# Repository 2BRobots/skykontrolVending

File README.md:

# skykontrolVending
This repository contains all the hardware and software used by 2BRobots to create and support IoT vending machines.

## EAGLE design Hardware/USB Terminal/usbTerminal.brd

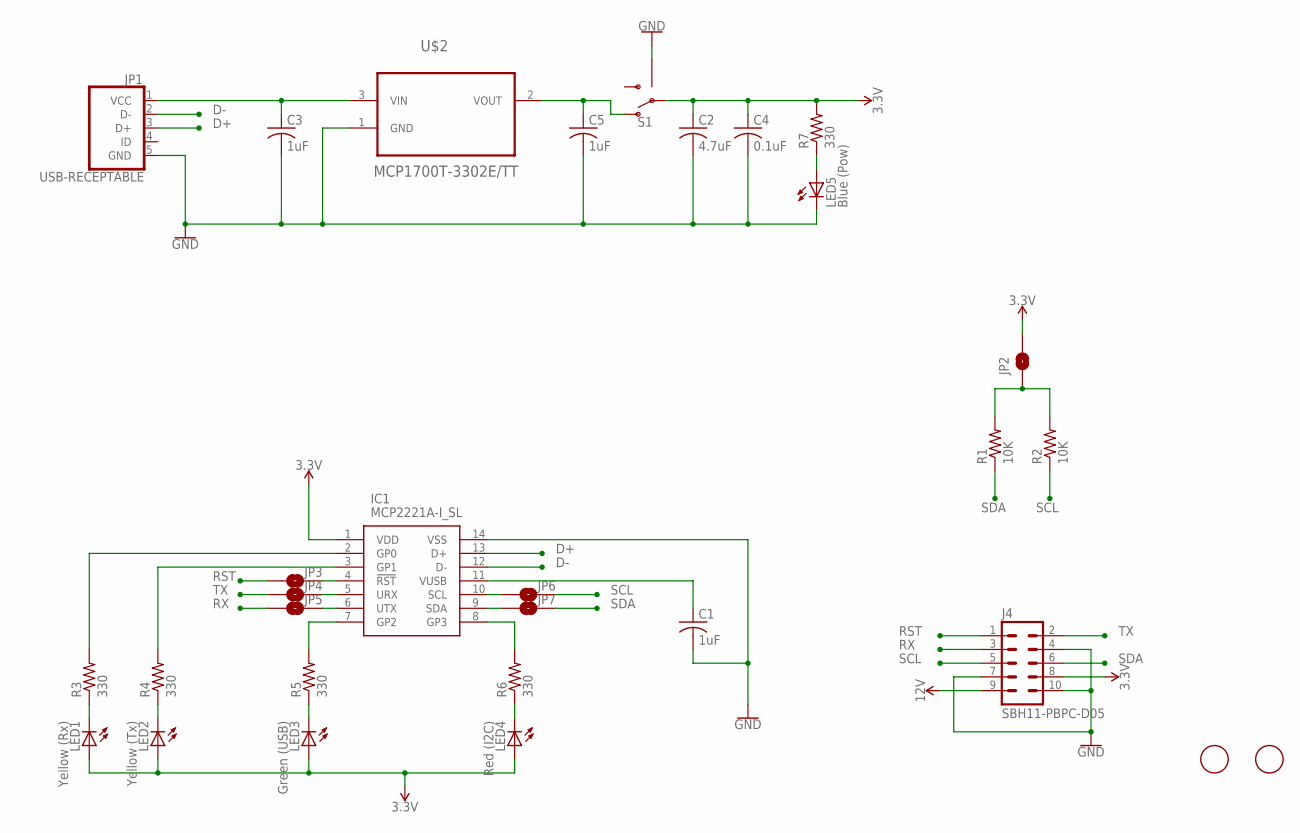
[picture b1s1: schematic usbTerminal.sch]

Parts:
C1, C3, C5: 1uF; C0603K
C2: 4.7uF; C0805K
C4: 0.1uF; C0603K
IC1: MCP2221A-I_SL; SOIC127P600X175-14N
J4: SBH11-PBPC-D05
JP1: USB-RECEPTABLE; FCI-10103594-0001LF
JP2, JP3, JP4, JP5, JP6, JP7: JUMPER-SMT_2_NO_SILK; SMT-JUMPER_2_NO_SILK
LED1: Yellow (Rx); CHIPLED_1206
LED2: Yellow (Tx); CHIPLED_1206
LED3: Green (USB); CHIPLED_1206
LED4: Red (I2C); CHIPLED_1206
LED5: Blue (Pow); CHIPLED_1206
R1, R2: 10K; R0805
R3, R4, R5, R6, R7: 330; R0805
S1: SWITCH-SPDT-SMD-RIGHT-ANGLE; SWITCH_SPST_SMD_A
U$1, U$3: FIDUCIAL; FIDUCIAL_1MM
U$2: MCP1700T-3302E/TT; SOT95P237X112-3N

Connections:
3.3V: C2.1, C4.1, IC1.1 (VDD), J4.8, JP2.2, LED1.A, LED2.A, LED3.A, LED4.A, R7.2, S1.2
12V: J4.9
D+: IC1.13 (D+), JP1.3 (D+)
D-: IC1.12 (D-), JP1.2 (D-)
GND: C1.2, C2.2, C3.2, C4.2, C5.2, IC1.14 (VSS), J4.4, J4.7, J4.10, JP1.5 (GND), LED5.C, S1.GND1 (GND), S1.GND2 (GND), S1.GND3 (GND), S1.GND4 (GND), U$2.1 (GND)
unnamed: IC1.4 (!RST), JP3.1
unnamed: C1.1, IC1.11 (VUSB)
unnamed: IC1.5 (URX), JP4.1
unnamed: JP2.1, R1.2, R2.2
unnamed: IC1.6 (UTX), JP5.1
unnamed: IC1.10 (SCL), JP6.2
unnamed: IC1.9 (SDA), JP7.2
unnamed: LED1.C, R3.1
unnamed: LED2.C, R4.1
unnamed: LED3.C, R5.1
unnamed: LED4.C, R6.1
unnamed: C3.1, JP1.1 (VCC), U$2.3 (VIN)
unnamed: LED5.A, R7.1
unnamed: IC1.7 (GP2), R5.2
unnamed: IC1.8 (GP3), R6.2
unnamed: IC1.3 (GP1), R4.2
unnamed: IC1.2 (GP0), R3.2
unnamed: C5.1, S1.1 (O), U$2.2 (VOUT)
RST: J4.1, JP3.2
RX: J4.3, JP5.2
SCL: J4.5, JP6.1, R2.1
SDA: J4.6, JP7.1, R1.1
TX: J4.2, JP4.2

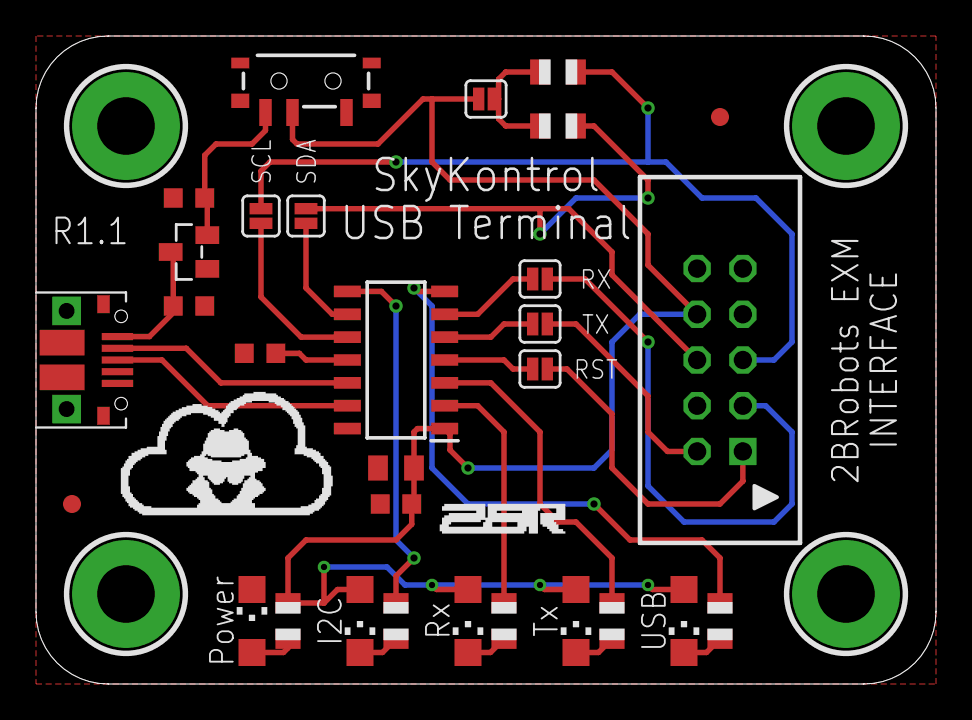
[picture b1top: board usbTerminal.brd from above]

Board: 2 copper layers, 50.0 x 36.0 mm, 30 parts (0 on the bottom side), 27 nets.

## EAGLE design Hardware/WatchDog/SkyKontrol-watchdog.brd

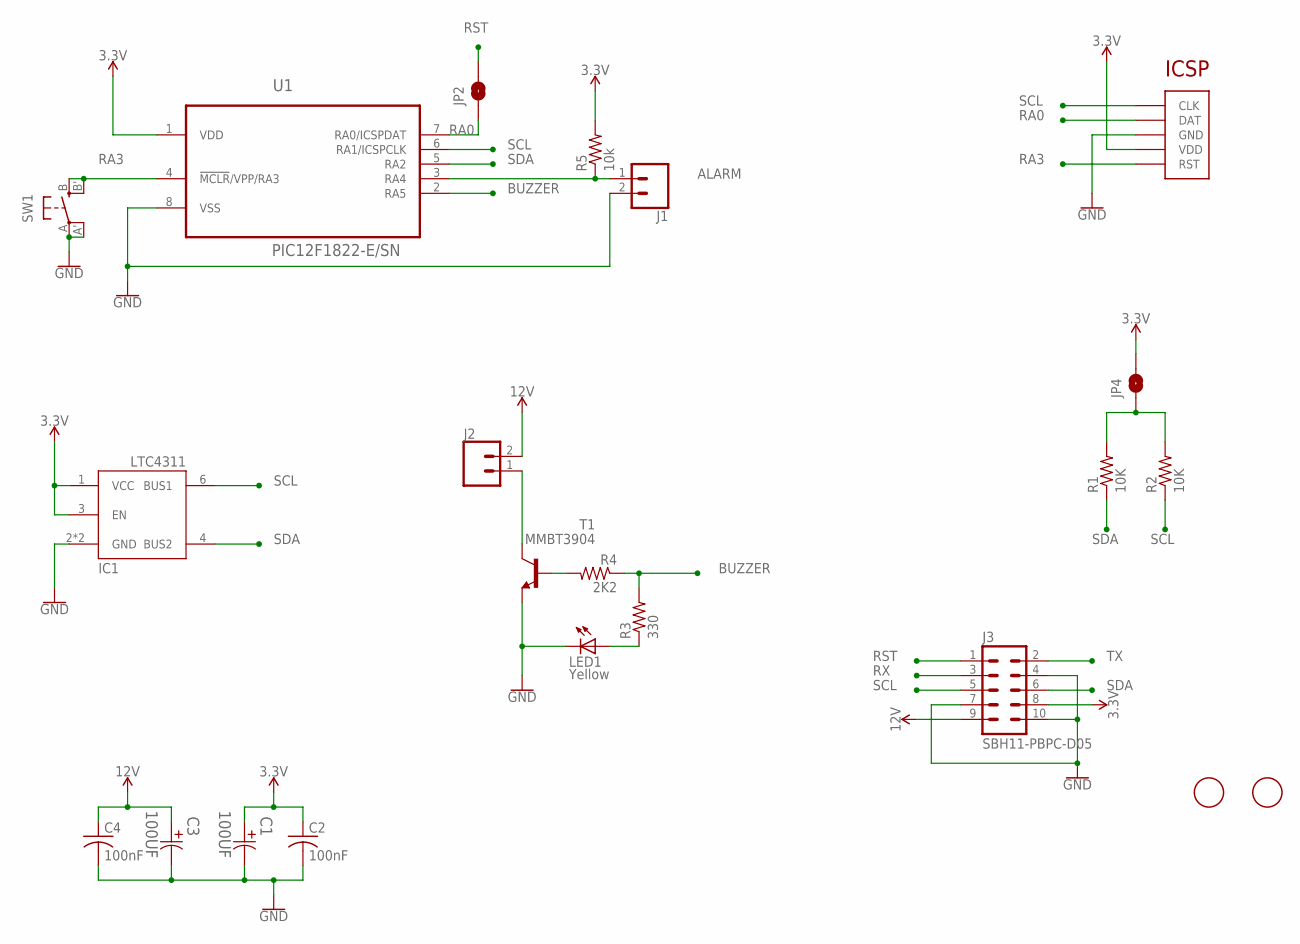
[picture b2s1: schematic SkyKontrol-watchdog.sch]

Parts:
C1, C3: 100UF; CAPAE660X800N
C2, C4: 100nF; C0603K
IC1: LTC4311_SC70; SC70-6L
J1, J2: CONN_025MM; SCREWTERMINAL-5MM-2
J3: SBH11-PBPC-D05
JP2, JP4: JUMPER-SMT_2_NO_SILK; SMT-JUMPER_2_NO_SILK
LED1: Yellow; CHIPLED_1206
R1, R2: 10K; R0805
R3: 330; R0805
R4: 2K2; R0805
R5: 10k; R0805
SW1: SPST_TACT-EVQQ2; EVQ-Q2
T1: MMBT3904; SOT23-BEC
U1: PIC12F1822-E/SN; SOIC127P600X175-8N
U$1, U$3: FIDUCIAL; FIDUCIAL_1MM
U$2: ICSP_POGO

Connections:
3.3V: C1.1, C2.1, IC1.1 (VCC), IC1.3 (EN), J3.8, JP4.2, R5.2, U1.1 (VDD), U$2.P$2 (VDD)
12V: C3.1, C4.1, J2.2, J3.9
ALARM: J1.1, R5.1, U1.3 (RA4)
BUZZER: R3.2, R4.1, U1.2 (RA5)
GND: C1.2, C2.2, C3.2, C4.2, IC1.2 (GND), IC1.5 (GND), J1.2, J3.4, J3.7, J3.10, LED1.C, SW1.A, SW1.A' (P1), T1.E, U1.8 (VSS), U$2.P$3 (GND)
unnamed: LED1.A, R3.1
unnamed: J2.1, T1.C
unnamed: JP4.1, R1.2, R2.2
unnamed: R4.2, T1.B
RA0: JP2.1, U1.7 (RA0/ICSPDAT), U$2.P$4 (DAT)
RA3: SW1.B (S), SW1.B' (S1), U1.4 (!MCLR!/VPP/RA3), U$2.P$1 (RST)
RST: J3.1, JP2.2
RX: J3.3
SCL: IC1.6 (BUS1), J3.5, R2.1, U1.6 (RA1/ICSPCLK), U$2.P$5 (CLK)
SDA: IC1.4 (BUS2), J3.6, R1.1, U1.5 (RA2)
TX: J3.2

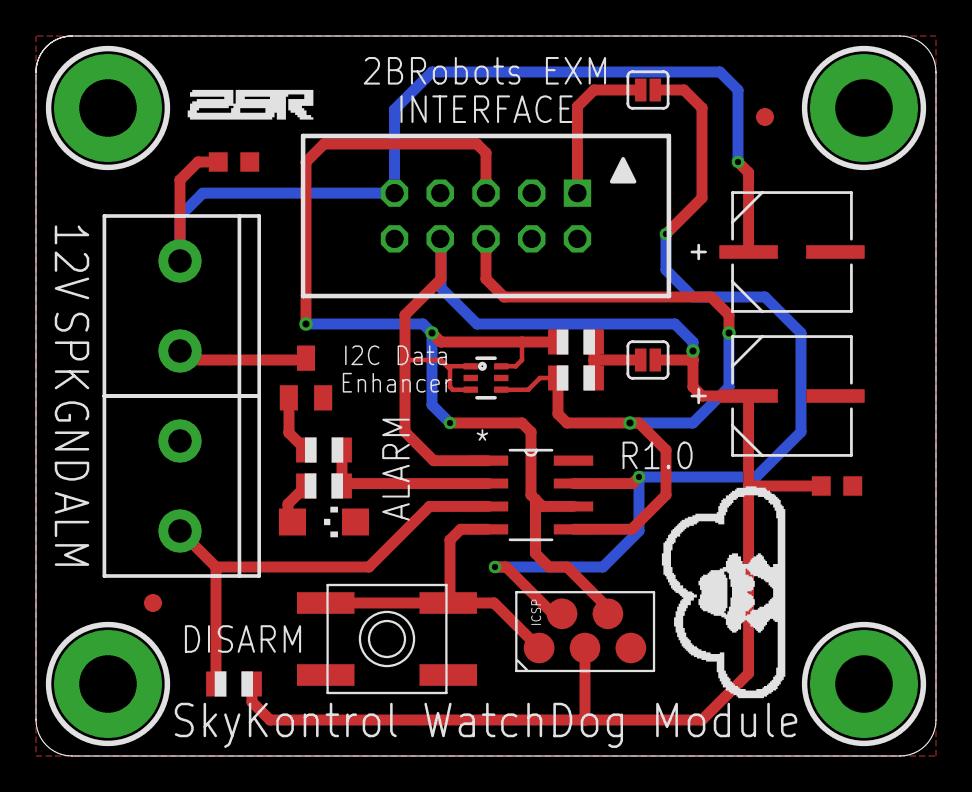
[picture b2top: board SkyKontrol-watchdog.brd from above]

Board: 2 copper layers, 50.0 x 40.0 mm, 22 parts (0 on the bottom side), 14 nets.

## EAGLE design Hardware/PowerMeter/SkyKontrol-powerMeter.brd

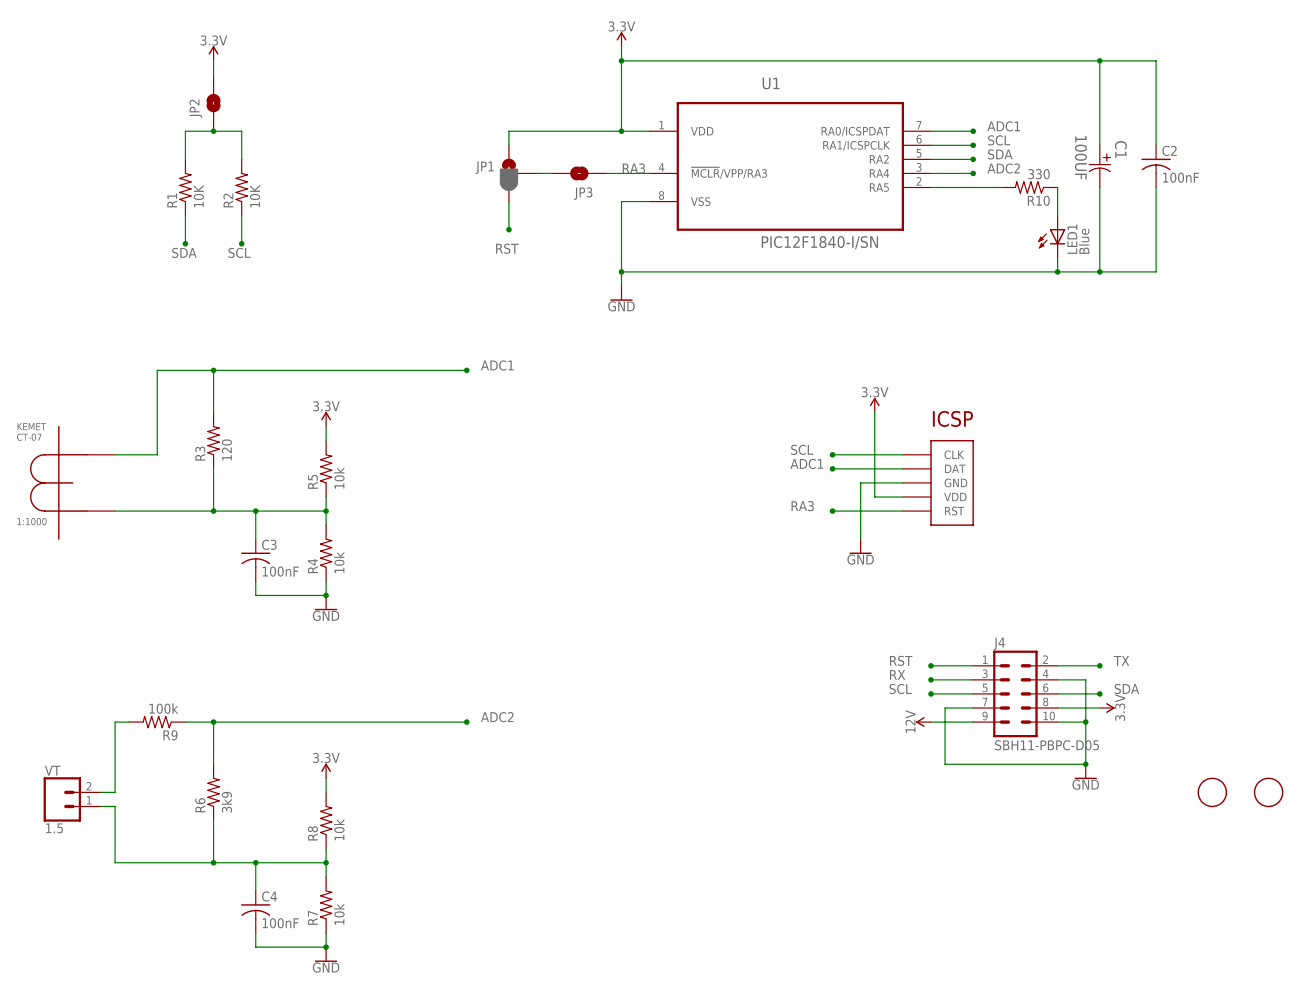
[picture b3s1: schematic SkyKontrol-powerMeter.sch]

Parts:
C1: 100UF; CAPAE660X800N
C2, C3, C4: 100nF; C0603K
J4: SBH11-PBPC-D05
JP1: JUMPER-SMT_3_1-NC_PASTE_SILK; SMT-JUMPER_3_1-NC_PASTE_SILK
JP2, JP3: JUMPER-SMT_2_NO_SILK; SMT-JUMPER_2_NO_SILK
LED1: Blue; CHIPLED_1206
R1, R2: 10K; R0805
R3: 120; R0805
R4, R5, R7, R8: 10k; R0805
R6: 3k9; R0805
R9: 100k; R0805
R10: 330; R0805
U1: PIC12F1840-I/SN; SOIC127P600X175-8N
U$1, U$3: FIDUCIAL; FIDUCIAL_1MM
U$2: ICSP_POGO
U$4: CT-07KEMET; CT-07
VT: 1.5; SCREWTERMINAL-5MM-2

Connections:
3.3V: C1.1, C2.1, J4.8, JP1.1, JP2.2, R5.2, R8.2, U1.1 (VDD), U$2.P$2 (VDD)
12V: J4.9
ADC1: R3.2, U1.7 (RA0/ICSPDAT), U$2.P$4 (DAT), U$4.P$1 (C1)
ADC2: R6.2, R9.1, U1.3 (RA4)
GND: C1.2, C2.2, C3.2, C4.2, J4.4, J4.7, J4.10, LED1.C, R4.1, R7.1, U1.8 (VSS), U$2.P$3 (GND)
unnamed: JP1.2, JP3.2
unnamed: C3.1, R3.1, R4.2, R5.1, U$4.P$2 (C2)
unnamed: R9.2, VT.2
unnamed: C4.1, R6.1, R7.2, R8.1, VT.1
unnamed: JP2.1, R1.2, R2.2
unnamed: R10.2, U1.2 (RA5)
unnamed: LED1.A, R10.1
RA3: JP3.1, U1.4 (!MCLR!/VPP/RA3), U$2.P$1 (RST)
RST: J4.1, JP1.3
RX: J4.3
SCL: J4.5, R2.1, U1.6 (RA1/ICSPCLK), U$2.P$5 (CLK)
SDA: J4.6, R1.1, U1.5 (RA2)
TX: J4.2

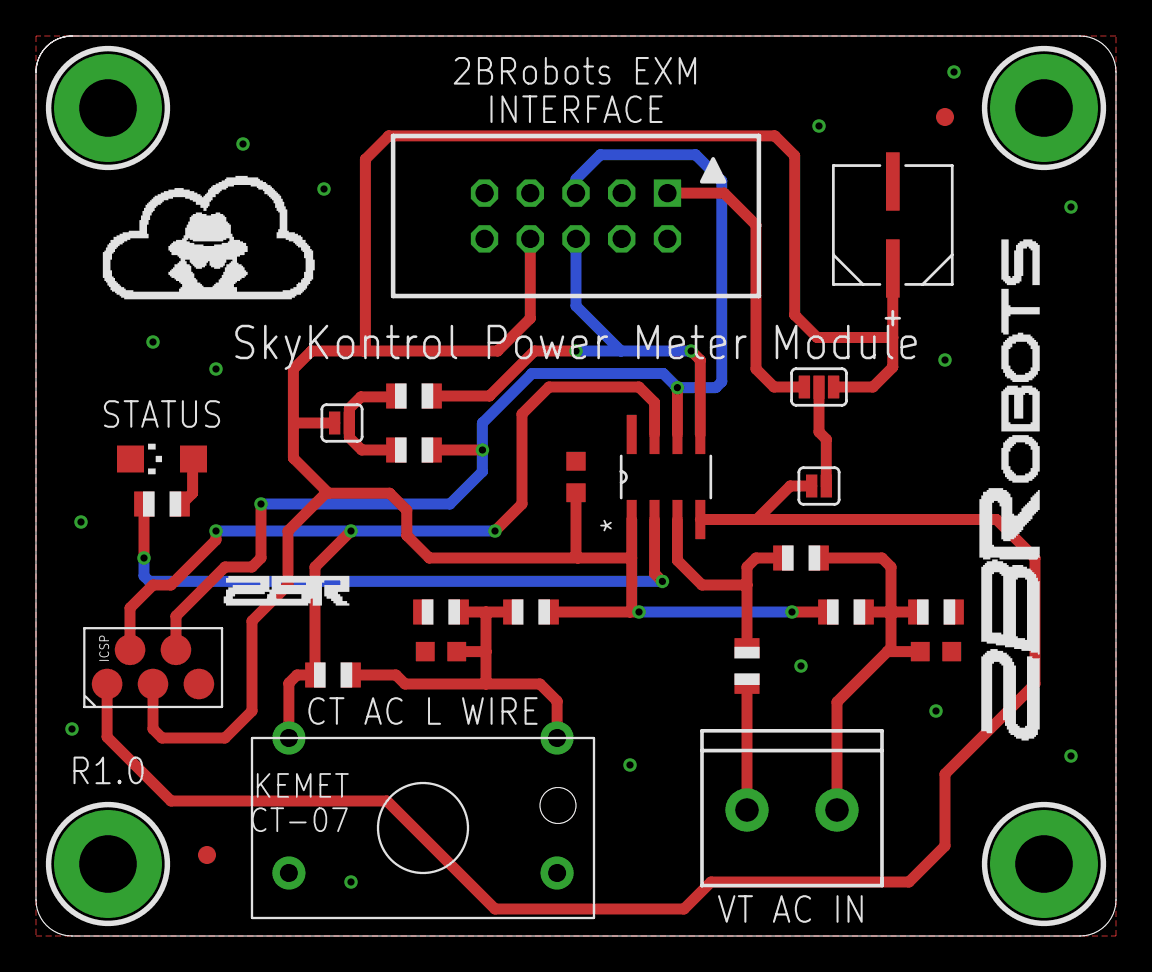
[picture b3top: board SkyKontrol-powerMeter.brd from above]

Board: 2 copper layers, 60.0 x 50.0 mm, 25 parts (0 on the bottom side), 15 nets.

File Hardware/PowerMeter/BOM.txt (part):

Part Value                        Device                       Package                      Description                                                                                                     CT-07  MPN             OC_FARNELL OC_NEWARK PACKAGE PIC POGO PROGRAMING SF_SKU    SMT SUPPLIER  TOLERANCE VALUE VOLTAGERATING
C1   100UF                        EEE-HA1E101XP-CASE-D8        CAPAE660X800N                Aluminum Electrolytic Capacitors,Surface Mount Type                                                                    EEE-HA1E101XP   1973328    58T9236   CASE-D8                                   PANASONIC ±20 %     100UF 25V          
C2   100nF                        C-USC0603K                   C0603K                       CAPACITOR, American symbol                                                                                                                                                                                                                   
C3   100nF                        C-USC0603K                   C0603K                       CAPACITOR, American symbol                                                                                                                                                                                                                   
C4   100nF                        C-USC0603K                   C0603K                       CAPACITOR, American symbol                                                                                                                                                                                                                   
J4   SBH11-PBPC-D05               SBH11-PBPC-D05               SBH11-PBPC-D05               HEADER - Vertical, Shrouded                                                                                                                                                                                                                  
JP1  JUMPER-SMT_3_1-NC_PASTE_SILK JUMPER-SMT_3_1-NC_PASTE_SILK SMT-JUMPER_3_1-NC_PASTE_SILK Normally closed solder jumper (1 of 2 connections)                                                                                                                                                                                           
JP2  JUMPER-SMT_2_NO_SILK         JUMPER-SMT_2_NO_SILK         SMT-JUMPER_2_NO_SILK         Normally open jumper                                                                                                                                                                                                                         
JP3  JUMPER-SMT_2_NO_SILK         JUMPER-SMT_2_NO_SILK         SMT-JUMPER_2_NO_SILK         Normally open jumper                                                                                                                                                                                                                         
LED1 Blue                         LEDCHIPLED_1206              CHIPLED_1206                 LED                                                                                                                                                                                                                                          
R1   10K                          R-US_R0805                   R0805                        RESISTOR, American symbol                                                                                                                                                                                                                    
R2   10K                          R-US_R0805                   R0805                        RESISTOR, American symbol                                                                                                                                                                                                                    
R3   120                          R-US_R0805                   R0805                        RESISTOR, American symbol                                                                                                                                                                                                                    
R4   10k                          R-US_R0805                   R0805                        RESISTOR, American symbol                                                                                                                                                                                                                    
R5   10k                          R-US_R0805                   R0805                        RESISTOR, American symbol                                                                                                                                                                                                                    
R6   3k9                          R-US_R0805                   R0805                        RESISTOR, American symbol                                                                                                                                                                                                                    
R7   10k                          R-US_R0805                   R0805                        RESISTOR, American symbol                                                                                                                                                                                                                    
R8   10k                          R-US_R0805                   R0805                        RESISTOR, American symbol                                                                                                                                                                                                                    
R9   100k                         R-US_R0805                   R0805                        RESISTOR, American symbol                                                                                                                                                                                                                    
R10  330                          R-US_R0805                   R0805                        RESISTOR, American symbol                                                                                                                                                                                                                    
U$1  FIDUCIAL                     FIDUCIAL                     FIDUCIAL_1MM                 For use by pick and place machines to calibrate the vision/machine, 1mm                                                                                                                                                                      
U$2  ICSP_POGO                    ICSP_POGO                    ICSP_POGO                                                                                                                                                                                                                                                                 
U$3  FIDUCIAL                     FIDUCIAL                     FIDUCIAL_1MM                 For use by pick and place machines to calibrate the vision/machine, 1mm                                                                                                                                                                      
U$4  CT-07KEMET                   CT-07KEMET                   CT-07                        The Kemet CT series low-alternating current sensors can be                                                      1:1000                                                                                                                       
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
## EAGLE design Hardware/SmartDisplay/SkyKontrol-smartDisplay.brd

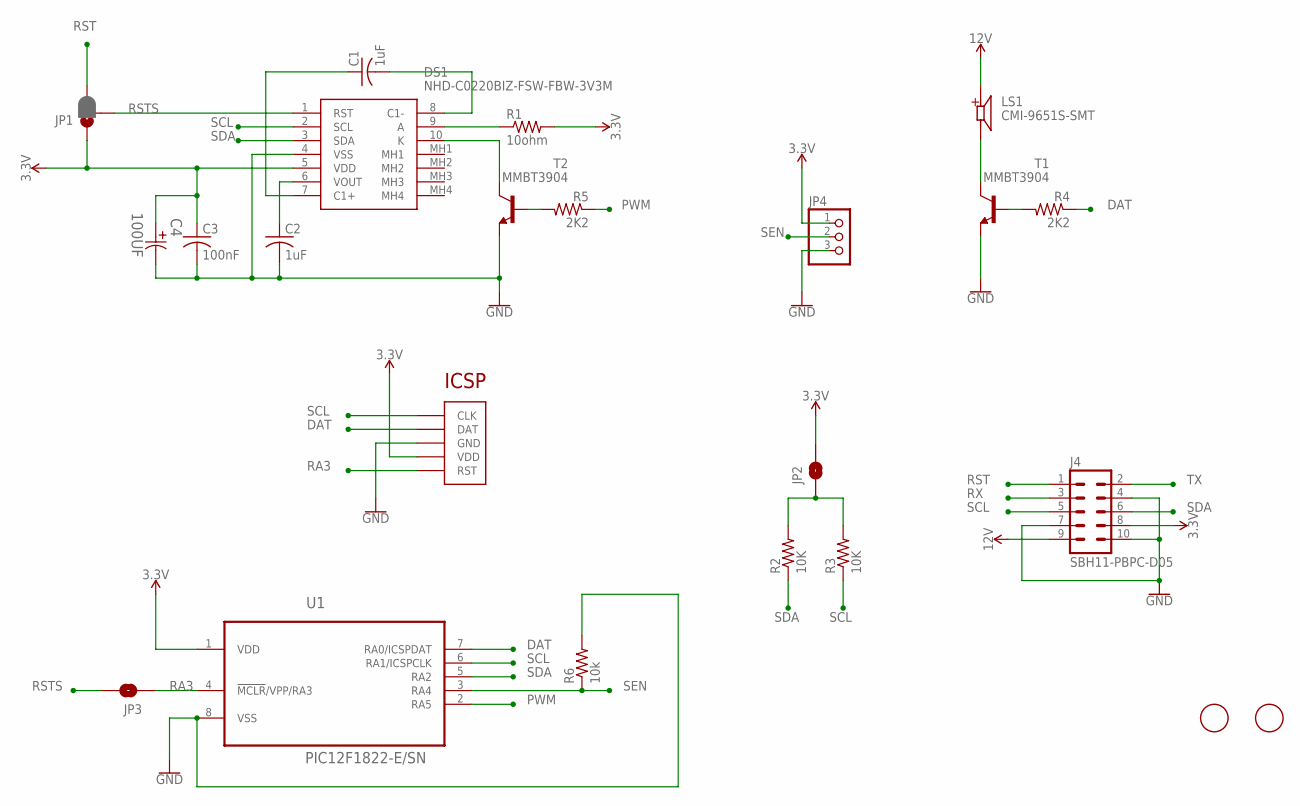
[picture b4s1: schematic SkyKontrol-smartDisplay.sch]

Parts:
C1, C2: 1uF; C0603K
C3: 100nF; C0603K
C4: 100UF; CAPAE660X800N
DS1: NHD-C0220BIZ-FSW-FBW-3V3M; NHDC0220BIZFSWFBW3V3M
J4: SBH11-PBPC-D05
JP1: JUMPER-SMT_3_1-NC_PASTE_SILK; SMT-JUMPER_3_1-NC_PASTE_SILK
JP2, JP3: JUMPER-SMT_2_NO_SILK; SMT-JUMPER_2_NO_SILK
JP4: PINHD-1X3CB; 1X03-CLEANBIG
LS1: CMI-9651S-SMT; CUI_CMI-9651S-SMT
R1: 10ohm; R0805
R2, R3: 10K; R0805
R4, R5: 2K2; R0805
R6: 10k; R0805
T1, T2: MMBT3904; SOT23-BEC
U1: PIC12F1822-E/SN; SOIC127P600X175-8N
U$1, U$3: FIDUCIAL; FIDUCIAL_1MM
U$2: ICSP_POGO

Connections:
3.3V: C3.1, C4.1, DS1.5 (VDD), J4.8, JP1.1, JP2.2, JP4.1, R1.2, U1.1 (VDD), U$2.P$2 (VDD)
12V: J4.9, LS1.P
DAT: R4.1, U1.7 (RA0/ICSPDAT), U$2.P$4 (DAT)
GND: C2.2, C3.2, C4.2, DS1.4 (VSS), J4.4, J4.7, J4.10, JP4.3, R6.2, T1.E, T2.E, U1.8 (VSS), U$2.P$3 (GND)
unnamed: C2.1, DS1.6 (VOUT)
unnamed: C1.2, DS1.8 (C1-)
unnamed: C1.1, DS1.7 (C1+)
unnamed: DS1.9 (A), R1.1
unnamed: JP2.1, R2.2, R3.2
unnamed: LS1.N, T1.C
unnamed: R4.2, T1.B
unnamed: DS1.10 (K), T2.C
unnamed: R5.2, T2.B
PWM: R5.1, U1.2 (RA5)
RA3: JP3.1, U1.4 (!MCLR!/VPP/RA3), U$2.P$1 (RST)
RST: J4.1, JP1.3
RSTS: DS1.1 (RST), JP1.2, JP3.2
RX: J4.3
SCL: DS1.2 (SCL), J4.5, R3.1, U1.6 (RA1/ICSPCLK), U$2.P$5 (CLK)
SDA: DS1.3 (SDA), J4.6, R2.1, U1.5 (RA2)
SEN: JP4.2, R6.1, U1.3 (RA4)
TX: J4.2

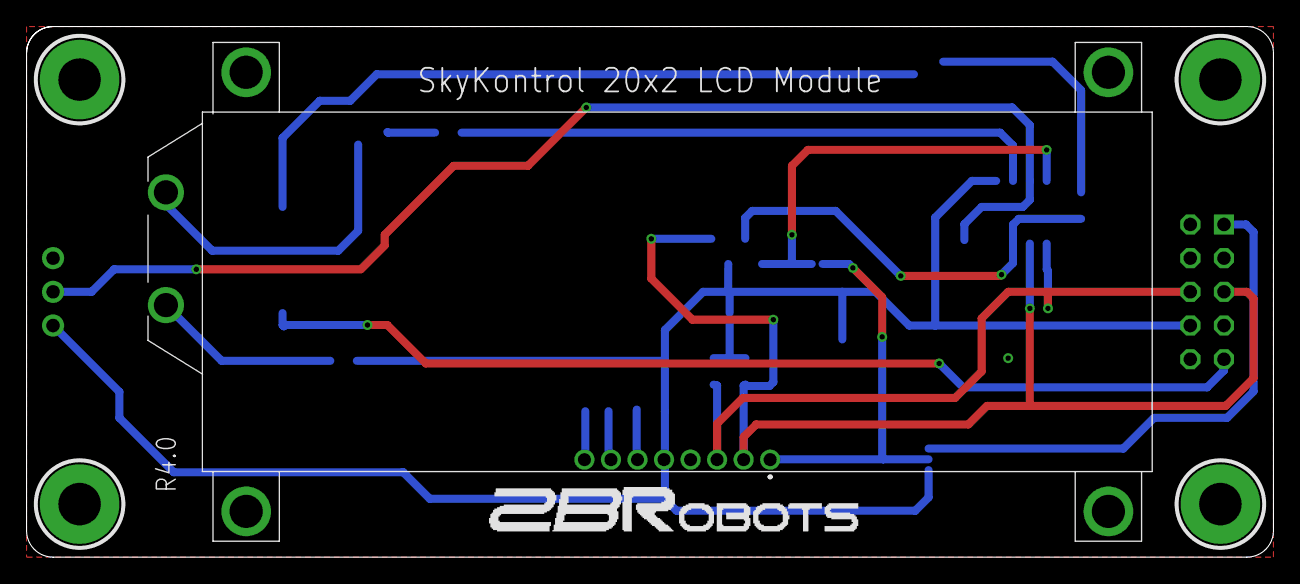
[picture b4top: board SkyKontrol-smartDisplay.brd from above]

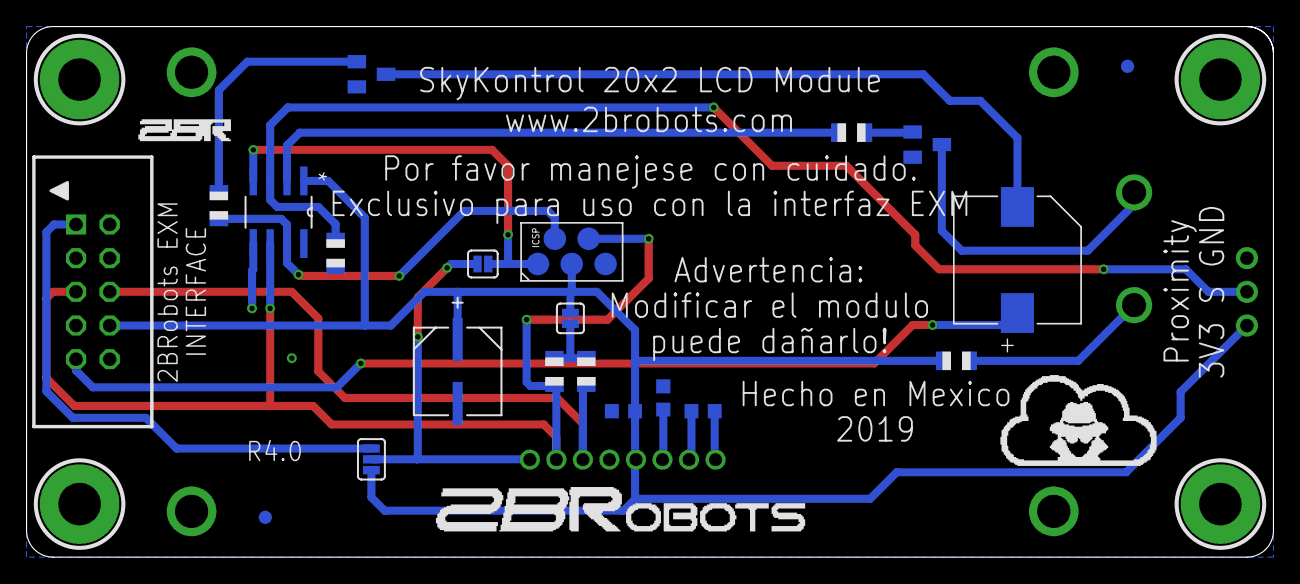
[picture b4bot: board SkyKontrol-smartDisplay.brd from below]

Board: 2 copper layers, 94.0 x 40.0 mm, 23 parts (21 on the bottom side), 20 nets.

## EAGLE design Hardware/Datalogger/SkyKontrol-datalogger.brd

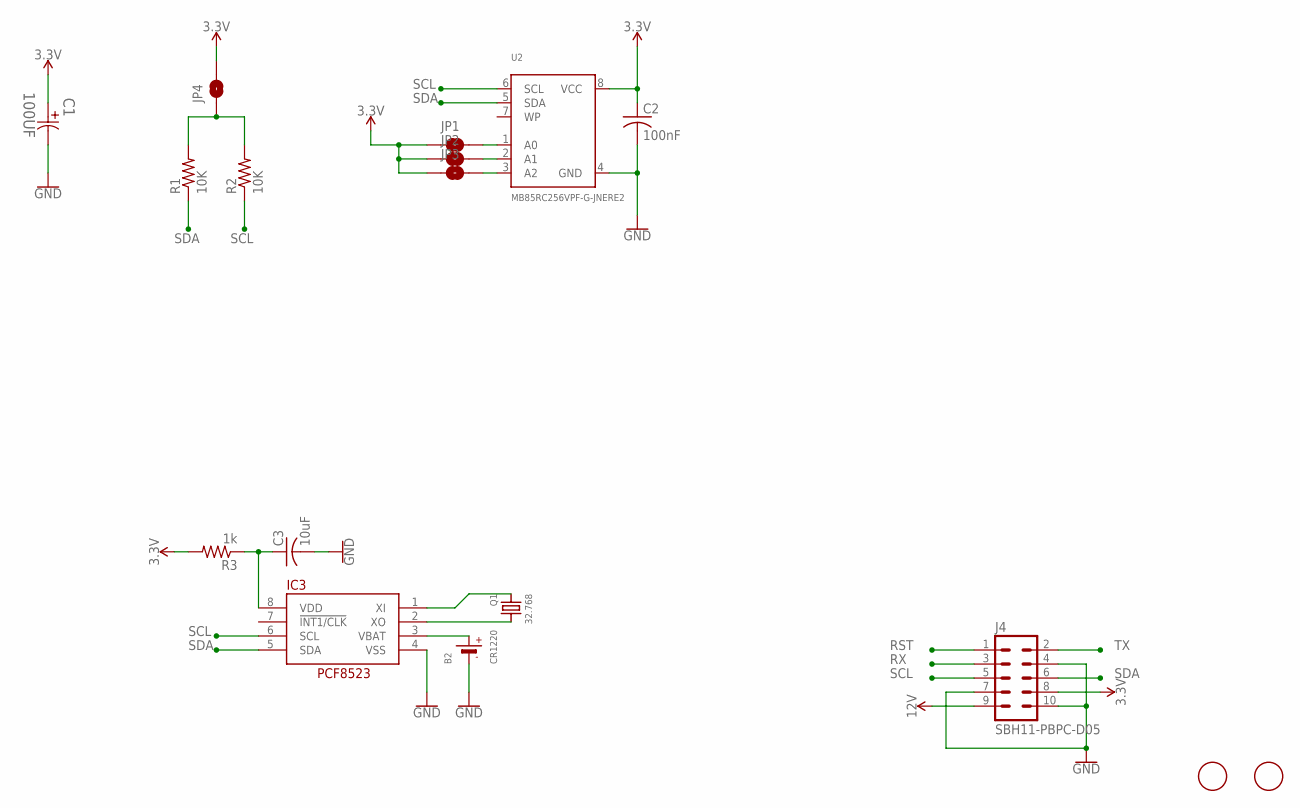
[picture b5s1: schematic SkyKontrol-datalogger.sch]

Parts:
B2: CR1220
C1: 100UF; CAPAE660X800N
C2: 100nF; C0603K
C3: 10uF; C0805K
IC3: RTC_PCF8523T; SOIC8_150MIL
J4: SBH11-PBPC-D05
JP1, JP2, JP3, JP4: JUMPER-SMT_2_NO_SILK; SMT-JUMPER_2_NO_SILK
Q1: 32.768; CRYSTAL_8X3.8
R1, R2: 10K; R0805
R3: 1k; R0805
U2: MB85RC256VPF-G-JNERE2; SOIC8_208MIL
U$1, U$3: FIDUCIAL; FIDUCIAL_1MM

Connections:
3.3V: C1.1, C2.1, J4.8, JP1.1, JP2.1, JP3.1, JP4.2, R3.2, U2.8 (VCC)
12V: J4.9
GND: B2.-, C1.2, C2.2, C3.2, IC3.4 (VSS), J4.4, J4.7, J4.10, U2.4 (GND)
unnamed: JP1.2, U2.1 (A0)
unnamed: JP2.2, U2.2 (A1)
unnamed: C3.1, IC3.8 (VDD), R3.1
unnamed: JP3.2, U2.3 (A2)
unnamed: JP4.1, R1.2, R2.2
unnamed: IC3.1 (XI), Q1.P$1 (1)
unnamed: IC3.2 (XO), Q1.P$4 (2)
RST: J4.1
RX: J4.3
SCL: IC3.6 (SCL), J4.5, R2.1, U2.6 (SCL)
SDA: IC3.5 (SDA), J4.6, R1.1, U2.5 (SDA)
TX: J4.2
VBAT1: B2.+$1 (+), IC3.3 (VBAT)

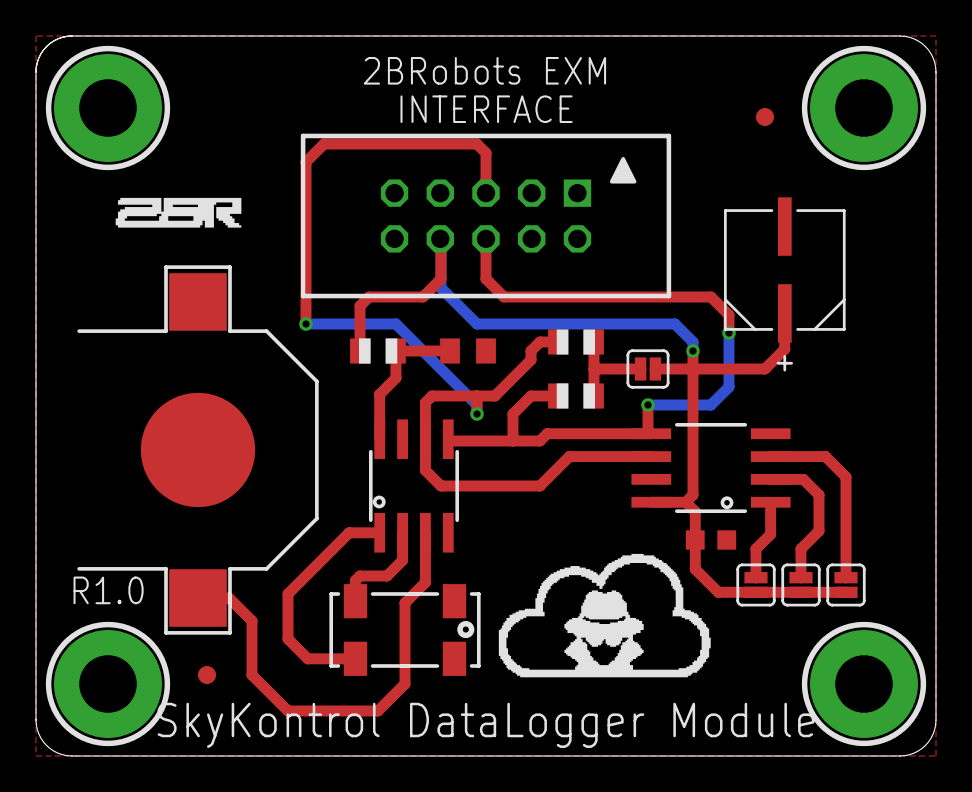
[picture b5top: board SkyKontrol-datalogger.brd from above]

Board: 2 copper layers, 50.0 x 40.0 mm, 17 parts (0 on the bottom side), 12 nets.

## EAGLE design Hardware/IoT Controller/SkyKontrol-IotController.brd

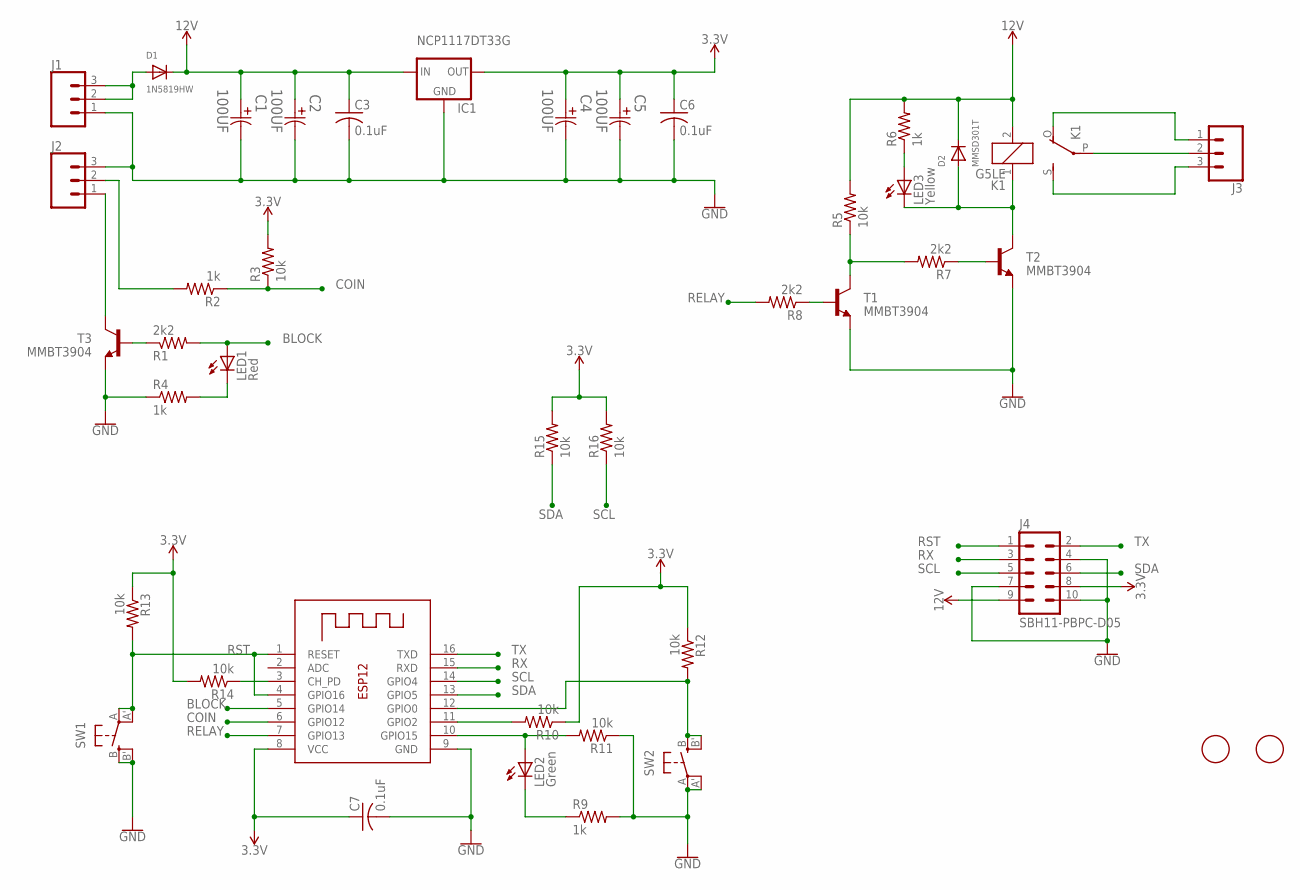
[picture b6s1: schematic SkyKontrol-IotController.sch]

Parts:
C1, C2, C4, C5: 100UF; CAPAE660X800N
C3, C6, C7: 0.1uF; C0603K
D1: 1N5819HW; SOD-123
D2: MMSD301T; SOD-123
IC1: NCP1117DT33G; TO252
J1, J2, J3: CONN_03-SCREW-5MM; SCREWTERMINAL-5MM-3
J4: SBH11-PBPC-D05
K1: G5LE
LED1: Red; CHIPLED_1206
LED2: Green; CHIPLED_1206
LED3: Yellow; CHIPLED_1206
R1, R7, R8: 2k2; R0805
R2, R4, R6, R9: 1k; R0805
R3, R5, R10, R11, R12, R13, R14, R15, R16: 10k; R0805
SW1, SW2: SPST_TACT-EVQQ2; EVQ-Q2
T1, T2, T3: MMBT3904; SOT23-BEC
U$1, U$2: FIDUCIAL; FIDUCIAL_1MM
X1: ESP-12

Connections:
3.3V: C4.1, C5.1, C6.1, C7.1, IC1.3 (OUT), J4.8, R3.2, R10.1, R12.1, R13.1, R14.2, R15.2, R16.2, X1.8 (VCC)
12V: C1.1, C2.1, C3.1, D1.C, D2.C, IC1.2 (IN), J4.9, K1.2, R5.2, R6.2
BLOCK: LED1.A, R1.2, X1.5 (GPIO14)
COIN: R2.1, R3.1, X1.6 (GPIO12)
GND: C1.2, C2.2, C3.2, C4.2, C5.2, C6.2, C7.2, IC1.1 (GND), J1.1, J2.3, J4.4, J4.7, J4.10, R4.1, R9.2, R11.1, SW1.B (S), SW1.B' (S1), SW2.A, SW2.A' (P1), T1.E, T2.E, T3.E, X1.9 (GND)
unnamed: LED1.C, R4.2
unnamed: J3.2, K1.P
unnamed: J2.1, T3.C
unnamed: J3.3, K1.S
unnamed: J3.1, K1.O
unnamed: D2.A, K1.1, LED3.C, T2.C
unnamed: J2.2, R2.2
unnamed: LED3.A, R6.1
unnamed: R7.1, T2.B
unnamed: R5.1, R7.2, T1.C
unnamed: R8.1, T1.B
unnamed: R1.1, T3.B
unnamed: R14.1, X1.3 (CH_PD)
unnamed: R12.2, SW2.B (S), SW2.B' (S1), X1.12 (GPIO0)
unnamed: D1.A, J1.2, J1.3
unnamed: LED2.C, R9.1
unnamed: LED2.A, R11.2, X1.10 (GPIO15)
unnamed: R10.2, X1.11 (GPIO2)
RELAY: R8.2, X1.7 (GPIO13)
RST: J4.1, R13.2, SW1.A, SW1.A' (P1), X1.1 (RESET), X1.4 (GPIO16)
RX: J4.3, X1.15 (RXD)
SCL: J4.5, R16.1, X1.14 (GPIO4)
SDA: J4.6, R15.1, X1.13 (GPIO5)
TX: J4.2, X1.16 (TXD)

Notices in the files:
parts and their libraries:
con-sullins: Copyright (C) 2009, Bob Starr
SparkFun-Jumpers: Licensing: Creative Commons ShareAlike 4.0 International - https://creativecommons.org/licenses/by-sa/4.0
